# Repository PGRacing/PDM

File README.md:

# PDM

Schematic mockup:

TODO on next PCB:

Rev 4.3
| ID | NAME | CAUSE |DIFFICULTY | PRIORITY | STATUS |
| --- | --- | --- | --- | --- | --- |
| 1. | Create test board for BTS50025-1TAE | Switch with higher Rds(on) should perform better in terms of diagnostics on most used loads | 1 | 3 | | 
| 2. | Create schematic and brd for imporoved power delivery section optimized for autmotive use based on MP4322 TLS850F2TAV50, TVS diodes + filtering | Current solution with MP2332 has maximum rating of 18V, which is really for load dumps | 3 | 3 || 
| 3. | Divide task to "safety critical real-time" hardware based (timer) ones and other normal operation tasks | Current solution can cause safety issus | 3 | 3 || 
| 4. | Prepare I^2t wiring harness protection | This should allow better WH protection| 3 | 2 || 
| 5. | Prepare OCP using curve, not only single value | This should allow better WH protection | 2 | 3 || 
| 6. | Use buffers for MCU protection | Protect MCU I/O pins | 1 | 2 || 
| 7. | Change zenner protection diodes to extended linearity region of Is switch output || 1 | 3 || 
| 8. | Add better filtering (change RC filter values) on Is output | Is output on inductive signals or fast switched signals HFreq PWM used causes invalid readings | 1 | 3 || 
| 9. | Detect battery under-voltage and UV shutdown for battery protection || 1 | 2 || 
| 10. | Configuration over USB | For sake of user-friendly solution | 3 | 2 || 
| 11. | CAN inputs support || 2 | 2 || 
| 12. | Thermal sensing | Safety critical | 2 | 2 || 
| 13. | Better 3D printed caseing (take care of screws outside of caseing envelope) + add honeycomb reinforcment | Safety critical for splash proof | 2 | 1 || 
| 14. | Add logic-level shifter for LED's | Some LED's turn red on random order | 1 | 3 || 
| 15. | Add separate voltage source for ARGB LED's and CAN bus | working can bus is critical for system integrity | 1 | 3 || 
| 16. | Add external voltage sources diagnosis (at least voltage on output) || 2 | 3 || 
| 17. | Add battery insulation and reverse-polarity + huge TVS and maybe Gas Discharge Tubes | Load dumps + cold crank etc. | 3 | 2 || 
| 18. | Add better connector for BAT+ | 1 | 3 || 
| 19. | Add limp home mode when any peripheral is malfunctioning (detect those malfunctions) | 2 | 3 || 
| 20. | Add TVS or zenner on all inputs (in limit of absolute maximium rating) near connector | 1 | 3 || 
| 21. | Add external or on-board probes for temperature sensing | 2 | 2 || 
| 22. | Add more state/debug led's | 1 | 1 || 
| 23. | Move safety functions oc and counters and errors into separate struct or bit mask of register | 2 | 3 || 

Rev. 4.1
| NAME | DIFFICULTY | PRIORITY | STATUS |
| --- | --- | --- | --- |
| 1. Add fuse for external sensors supply (100mA). Can also be solved with second 5V regulator for sensors + fuse. | 1 | 3 | DONE - Added external LDO's to 3.3V and 5V |
| 2. Change CPC1117N to CPC1017N (or diffrent PhotoMos) | 1 | 2 | DONE - Added diffrent (smaller) Opto-MOS |
| 3. Add clamping diodes on any signals | 2 | 3 | Added zenner + shottky clippers |
| 4. Change input filtration for low profile SMD capacitor instead of tht | 1 | 1 | DEPRECEATED  |
| 5. Add SWO pin | 2 | 2 | DONE |
| 6. Current sensors output should be collected by one ADC !!! - for eg. ADC3 (change pinout) | 3 | 2 | DONE |
| 7. Add clamping diodes on current sensor to allow lower range current detecion | 2 | 3 | DONE |
| 8. Selection and redirection of IO is not imporant | 1 | 1 | DONE - (only four channels) |
| 9. Fix WS2812B footprint | 1 | 3 | DONE |
| 10. Use smaller footprint for voltage mux and can transceiver | 2 | 1 | DONE - changed voltage mux to 16 channel, CAN transceiver same |
| 11. Change FET's to BTS50010-1LUA | 3 | 2 |  DONE |
| 12. Add RX/TX information leds to CAN bus (software driven) | 1 | 1 | DEPERECATED |
| 13. Add MUX for mutlichannel switch | 2 | 2 | DONE - added 16 channel mux |
| 14. Add CAN software switching | 2 | 2 | DONE |
| 14. Remove additional header for stlink | 2 | 2 | DONE |

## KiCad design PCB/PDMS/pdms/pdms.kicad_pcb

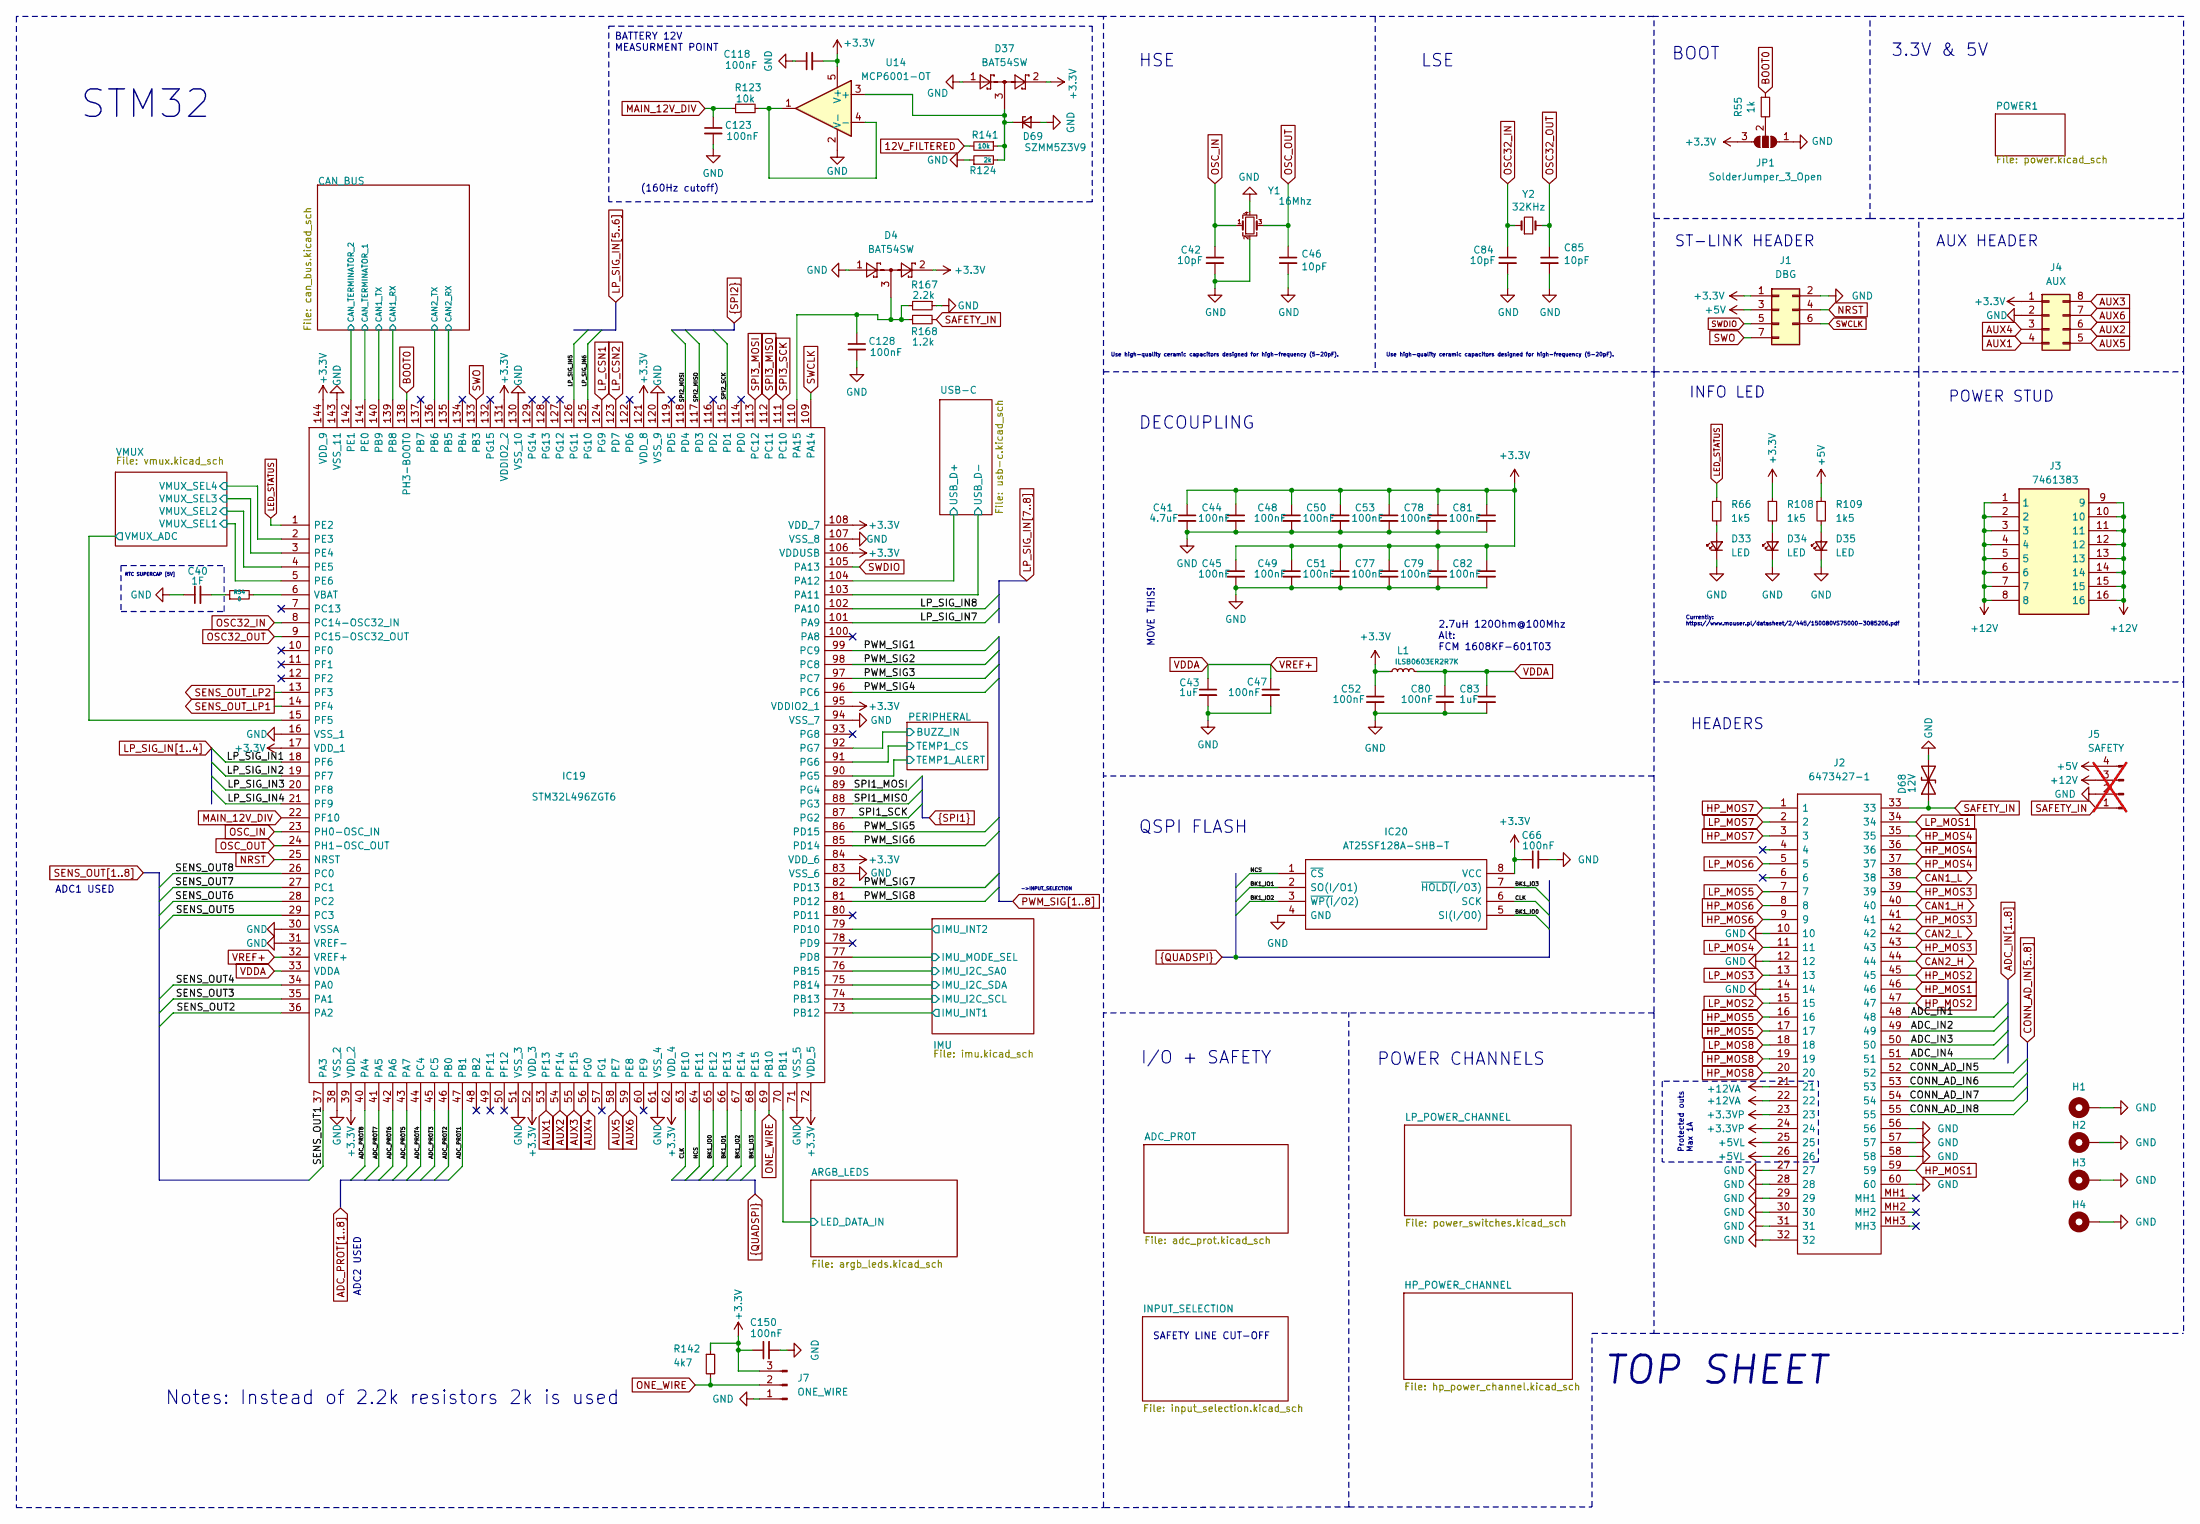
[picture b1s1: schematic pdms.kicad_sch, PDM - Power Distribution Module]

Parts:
C40: 1F; CAPCP3225X100N
C41: 4.7uF; R_0402_1005Metric
C42, C46: 10pF; R_0402_1005Metric
C43: 1uF; R_0402_1005Metric
C44, C45, C47, C48, C49, C50, C51, C52, C53, C66, C150: 100nF; R_0402_1005Metric
C77, C78, C79, C80, C81, C82, C118, C123, C128: 100nF; C_0402_1005Metric
C83: 1uF; C_0402_1005Metric
C84, C85: 10pF; C_0402_1005Metric
D4, D37: BAT54SW; SOT-323_SC-70
D33: LED; LED_0402_1005Metric
D34, D35: LED; LED_0805_2012Metric
D68: 12V; D_SOD-323
D69: SZMM5Z3V9; D_SOD-523
H1, H2, H3, H4: MountingHole_Pad; MountingHole_3.2mm_M3_Pad_Via
IC19: STM32L496ZGT6; QFP50P2200X2200X160-144N; Manufacturer_Part_Number STM32L496ZGT6; Mouser Part Number 511-STM32L496ZGT6
IC20: AT25SF128A-SHB-T; SOIC127P798X216-8N; Manufacturer_Part_Number AT25SF128A-SHB-T; Mouser Part Number 988-AT25SF128A-SHB-T
J1: DBG; Molex_PicoBlade_53047-0710_1x07_P1.25mm_Vertical
J2: 6473427-1; 64734271; Manufacturer_Part_Number 6473427-1; Mouser Part Number 571-6473427-1
J3: 7461383; Manufacturer_Part_Number 7461383; Mouser Part Number 710-7461383
J4: AUX; PinHeader_2x04_P1.00mm_Vertical_SMD
J5: SAFETY; Molex_PicoBlade_53047-0410_1x04_P1.25mm_Vertical; not fitted
J7: ONE_WIRE; PinHeader_1x03_P2.00mm_Vertical
JP1: SolderJumper_3_Open; SolderJumper-3_P1.3mm_Open_Pad1.0x1.5mm
L1: ILSB0603ER2R7K; L_0603_1608Metric
R54: 0; R_0805_2012Metric
R55: 1k; R_0402_1005Metric
R66, R108, R109: 1k5; R_0402_1005Metric
R123, R141: 10k; R_0402_1005Metric
R124: 2k; R_0402_1005Metric
R142: 4k7; R_0402_1005Metric
R167: 2.2k; R_0402_1005Metric
R168: 1.2k; R_0402_1005Metric
U14: MCP6001-OT; SOT-23-5
Y1: 16Mhz; Crystal_SMD_2016-4Pin_2.0x1.6mm
Y2: 32KHz; Crystal_SMD_3215-2Pin_3.2x1.5mm

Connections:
+3.3VP: J2.23, J2.24; also elsewhere on the board
+5V: J1.3, J5.4, R109.1; also elsewhere on the board
+5VL: J2.25, J2.26; also elsewhere on the board
+12V: J3.1, J3.2, J3.3, J3.4, J3.5, J3.6, J3.7, J3.8, J3.9, J3.10, J3.11, J3.12, J3.13, J3.14, J3.15, J3.16, J5.3; also elsewhere on the board
+12VA: J2.21, J2.22; also elsewhere on the board
/ARGB_LEDS/LED_DATA_IN: IC19.70 (PB11); also elsewhere on the board
/CAN_BUS/CAN1_RX: IC19.139 (PB8); also elsewhere on the board
/CAN_BUS/CAN1_TX: IC19.140 (PB9); also elsewhere on the board
/CAN_BUS/CAN2_RX: IC19.135 (PB5); also elsewhere on the board
/CAN_BUS/CAN2_TX: IC19.136 (PB6); also elsewhere on the board
/CAN_BUS/CAN_TERMINATOR_1: IC19.141 (PE0); also elsewhere on the board
/CAN_BUS/CAN_TERMINATOR_2: IC19.142 (PE1); also elsewhere on the board
/IMU/IMU_I2C_SA0: IC19.76 (PB15); also elsewhere on the board
/IMU/IMU_I2C_SCL: IC19.74 (PB13); also elsewhere on the board
/IMU/IMU_I2C_SDA: IC19.75 (PB14); also elsewhere on the board
/IMU/IMU_INT1: IC19.73 (PB12); also elsewhere on the board
/IMU/IMU_INT2: IC19.79 (PD10); also elsewhere on the board
/IMU/IMU_MODE_SEL: IC19.77 (PD8); also elsewhere on the board
/PERIPHERAL/BUZZ_IN: IC19.92 (PG7); also elsewhere on the board
/PERIPHERAL/TEMP1_ALERT: IC19.90 (PG5); also elsewhere on the board
/PERIPHERAL/TEMP1_CS: IC19.91 (PG6); also elsewhere on the board
/USB-C/USB_D+: IC19.104 (PA12); also elsewhere on the board
/USB-C/USB_D-: IC19.103 (PA11); also elsewhere on the board
/VMUX/VMUX_SEL1: IC19.5 (PE6); also elsewhere on the board
/VMUX/VMUX_SEL2: IC19.4 (PE5); also elsewhere on the board
/VMUX/VMUX_SEL3: IC19.3 (PE4); also elsewhere on the board
/VMUX/VMUX_SEL4: IC19.2 (PE3); also elsewhere on the board
ADC_IN1: J2.48; also elsewhere on the board
ADC_IN2: J2.49; also elsewhere on the board
ADC_IN3: J2.50; also elsewhere on the board
ADC_IN4: J2.51; also elsewhere on the board
ADC_PROT1: IC19.47 (PB1); also elsewhere on the board
ADC_PROT2: IC19.46 (PB0); also elsewhere on the board
ADC_PROT3: IC19.45 (PC5); also elsewhere on the board
ADC_PROT4: IC19.44 (PC4); also elsewhere on the board
ADC_PROT5: IC19.43 (PA7); also elsewhere on the board
ADC_PROT6: IC19.42 (PA6); also elsewhere on the board
ADC_PROT7: IC19.41 (PA5); also elsewhere on the board
ADC_PROT8: IC19.40 (PA4); also elsewhere on the board
AUX1: IC19.53 (PF13), J4.4
AUX2: IC19.54 (PF14), J4.6
AUX3: IC19.55 (PF15), J4.8
AUX4: IC19.56 (PG0), J4.3
AUX5: IC19.58 (PE7), J4.5
AUX6: IC19.59 (PE8), J4.7
BK1_IO0: IC19.65 (PE12), IC20.5 (SI(I/O0))
BK1_IO1: IC19.66 (PE13), IC20.2 (SO(I/O1))
BK1_IO2: IC19.67 (PE14), IC20.3 (~WP(I/O2))
BK1_IO3: IC19.68 (PE15), IC20.7 (~HOLD(I/O3))
BOOT0: IC19.138 (PH3-BOOT0), R55.1
CAN1_H: J2.40; also elsewhere on the board
CAN1_L: J2.38; also elsewhere on the board
CAN2_H: J2.44; also elsewhere on the board
CAN2_L: J2.42; also elsewhere on the board
CLK: IC19.63 (PE10), IC20.6 (SCK)
CONN_AD_IN5: J2.52; also elsewhere on the board
CONN_AD_IN6: J2.53; also elsewhere on the board
CONN_AD_IN7: J2.54; also elsewhere on the board
CONN_AD_IN8: J2.55; also elsewhere on the board
HP_MOS1: J2.46, J2.59; also elsewhere on the board
HP_MOS2: J2.45, J2.47; also elsewhere on the board
HP_MOS3: J2.39, J2.41, J2.43; also elsewhere on the board
HP_MOS4: J2.35, J2.36, J2.37; also elsewhere on the board
HP_MOS5: J2.16, J2.17; also elsewhere on the board
HP_MOS6: J2.8, J2.9; also elsewhere on the board
HP_MOS7: J2.1, J2.3; also elsewhere on the board
HP_MOS8: J2.19, J2.20; also elsewhere on the board
LED_STATUS: IC19.1 (PE2), R66.1
LP_CSN1: IC19.124 (PG9); also elsewhere on the board
LP_CSN2: IC19.123 (PD7); also elsewhere on the board
LP_MOS1: J2.34; also elsewhere on the board
LP_MOS2: J2.15; also elsewhere on the board
LP_MOS3: J2.13; also elsewhere on the board
LP_MOS4: J2.11; also elsewhere on the board
LP_MOS5: J2.7; also elsewhere on the board
LP_MOS6: J2.5; also elsewhere on the board
LP_MOS7: J2.2; also elsewhere on the board
LP_MOS8: J2.18; also elsewhere on the board
LP_SIG_IN1: IC19.18 (PF6); also elsewhere on the board
LP_SIG_IN2: IC19.19 (PF7); also elsewhere on the board
LP_SIG_IN3: IC19.20 (PF8); also elsewhere on the board
LP_SIG_IN4: IC19.21 (PF9); also elsewhere on the board
LP_SIG_IN5: IC19.126 (PG11); also elsewhere on the board
LP_SIG_IN6: IC19.125 (PG10); also elsewhere on the board
LP_SIG_IN7: IC19.101 (PA9); also elsewhere on the board
LP_SIG_IN8: IC19.102 (PA10); also elsewhere on the board
NCS: IC19.64 (PE11), IC20.1 (~CS)
NRST: IC19.25 (NRST), J1.4
unnamed: C40.2, R54.1
unnamed: D33.2 (A), R66.2
unnamed: D34.2 (A), R108.2
unnamed: D35.2 (A), R109.2
unnamed: C128.1, D4.3, IC19.110 (PA15), R167.2, R168.1
unnamed: IC19.6 (VBAT), R54.2
unnamed: JP1.2 (C), R55.2
ONE_WIRE: IC19.69 (PB10), J7.2, R142.2
OSC32_IN: C84.1, IC19.8 (PC14-OSC32_IN), Y2.1
OSC32_OUT: C85.1, IC19.9 (PC15-OSC32_OUT), Y2.2
OSC_IN: C42.1, IC19.23 (PH0-OSC_IN), Y1.1
OSC_OUT: C46.1, IC19.24 (PH1-OSC_OUT), Y1.3
PWM_SIG1: IC19.99 (PC9); also elsewhere on the board
PWM_SIG2: IC19.98 (PC8); also elsewhere on the board
PWM_SIG3: IC19.97 (PC7); also elsewhere on the board
PWM_SIG4: IC19.96 (PC6); also elsewhere on the board
PWM_SIG5: IC19.86 (PD15); also elsewhere on the board
PWM_SIG6: IC19.85 (PD14); also elsewhere on the board
PWM_SIG7: IC19.82 (PD13); also elsewhere on the board
PWM_SIG8: IC19.81 (PD12); also elsewhere on the board
SAFETY_IN: D68.1 (A1), J2.33, J5.1, R168.2; also elsewhere on the board
SENS_OUT1: IC19.37 (PA3); also elsewhere on the board
SENS_OUT2: IC19.36 (PA2); also elsewhere on the board
SENS_OUT3: IC19.35 (PA1); also elsewhere on the board
SENS_OUT4: IC19.34 (PA0); also elsewhere on the board
SENS_OUT5: IC19.29 (PC3); also elsewhere on the board
SENS_OUT6: IC19.28 (PC2); also elsewhere on the board
SENS_OUT7: IC19.27 (PC1); also elsewhere on the board
SENS_OUT8: IC19.26 (PC0); also elsewhere on the board
SENS_OUT_LP1: IC19.14 (PF4); also elsewhere on the board
SENS_OUT_LP2: IC19.13 (PF3); also elsewhere on the board
SPI1_MISO: IC19.88 (PG3); also elsewhere on the board
SPI1_MOSI: IC19.89 (PG4); also elsewhere on the board
SPI1_SCK: IC19.87 (PG2); also elsewhere on the board
SPI2_MISO: IC19.117 (PD3); also elsewhere on the board
SPI2_MOSI: IC19.118 (PD4); also elsewhere on the board
SPI2_SCK: IC19.115 (PD1); also elsewhere on the board
SPI3_MISO: IC19.112 (PC11)
SPI3_MOSI: IC19.113 (PC12)
SPI3_SCK: IC19.111 (PC10)
SWCLK: IC19.109 (PA14), J1.6; also elsewhere on the board
SWDIO: IC19.105 (PA13), J1.5; also elsewhere on the board
SWO: IC19.133 (PB3), J1.7

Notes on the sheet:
BATTERY 12V MEASURMENT POINT
POWER STUD
BOOT
AUX HEADER
HSE
MOVE THIS!
Notes: Instead of 2.2k resistors 2k is used
INFO LED
STM32
DECOUPLING
POWER CHANNELS
(160Hz cutoff)
->INPUT_SELECTION
2.7uH 120Ohm@100Mhz Alt: FCM 1608KF-601T03
Use high-quality ceramic capacitors designed for high-frequency (5-20pF).
QSPI FLASH
Protected outs Max 1A
TOP SHEET
RTC SUPERCAP [5V]
HEADERS
ST-LINK HEADER
LSE
I/O + SAFETY
SAFETY LINE CUT-OFF
Currently: https://www.mouser.pl/datasheet/2/445/150080VS75000-3085206.pdf
ADC2 USED
ADC1 USED
3.3V & 5V

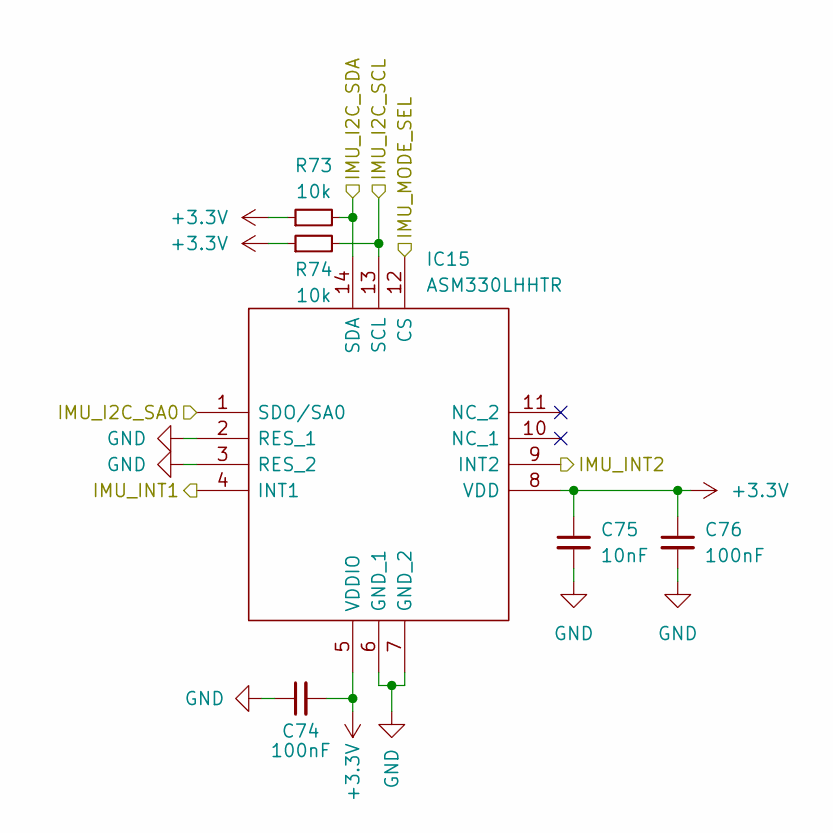
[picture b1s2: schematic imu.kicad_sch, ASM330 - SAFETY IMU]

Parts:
C74, C76: 100nF; C_0402_1005Metric
C75: 10nF; C_0402_1005Metric
IC15: ASM330LHHTR; LGA-14_2.5X3X0.86_; Manufacturer_Part_Number ASM330LHHTR; Mouser Part Number 511-ASM330LHHTR
R73, R74: 10k; R_0402_1005Metric

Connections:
/IMU/IMU_I2C_SA0: IC15.1 (SDO/SA0); also elsewhere on the board
/IMU/IMU_I2C_SCL: IC15.13 (SCL), R74.2; also elsewhere on the board
/IMU/IMU_I2C_SDA: IC15.14 (SDA), R73.2; also elsewhere on the board
/IMU/IMU_INT1: IC15.4 (INT1); also elsewhere on the board
/IMU/IMU_INT2: IC15.9 (INT2); also elsewhere on the board
/IMU/IMU_MODE_SEL: IC15.12 (CS); also elsewhere on the board

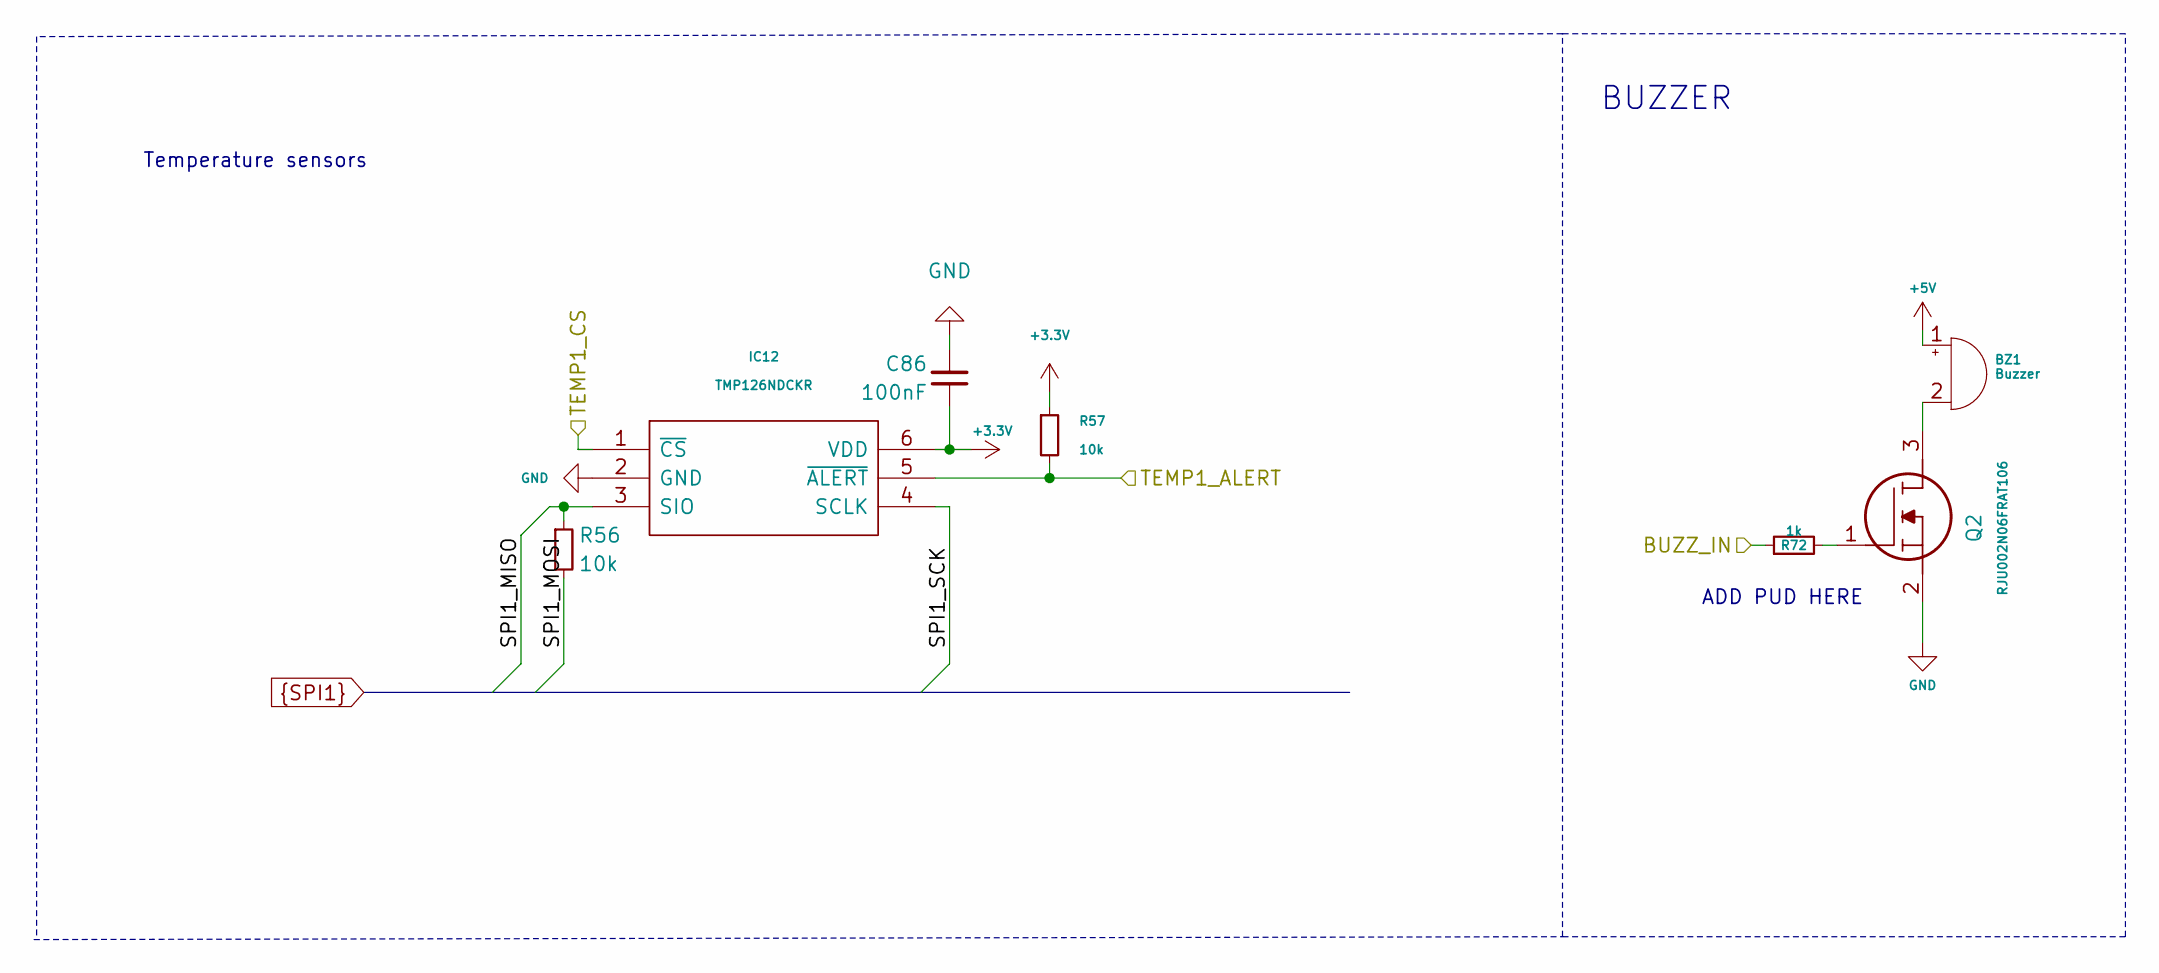
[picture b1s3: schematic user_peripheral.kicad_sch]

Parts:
BZ1: Buzzer; Buzzer_12x9.5RM7.6
C86: 100nF; C_0402_1005Metric
IC12: TMP126NDCKR; SOT65P210X110-6N; Manufacturer_Part_Number TMP126NDCKR; Mouser Part Number 595-TMP126NDCKR
Q2: RJU002N06FRAT106; SOT65P210X110-3N; Manufacturer_Part_Number RJU002N06FRAT106; Mouser Part Number 755-RJU002N06FRAT106
R56, R57: 10k; R_0402_1005Metric
R72: 1k; R_0402_1005Metric

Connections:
+5V: BZ1.1 (-); also elsewhere on the board
/PERIPHERAL/BUZZ_IN: R72.1; also elsewhere on the board
/PERIPHERAL/TEMP1_ALERT: IC12.5 (~ALERT), R57.2; also elsewhere on the board
/PERIPHERAL/TEMP1_CS: IC12.1 (~CS); also elsewhere on the board
unnamed: BZ1.2 (+), Q2.3
unnamed: Q2.1, R72.2
SPI1_MISO: IC12.3 (SIO), R56.1; also elsewhere on the board
SPI1_MOSI: R56.2; also elsewhere on the board
SPI1_SCK: IC12.4 (SCLK); also elsewhere on the board

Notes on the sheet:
BUZZER
ADD PUD HERE
Temperature sensors

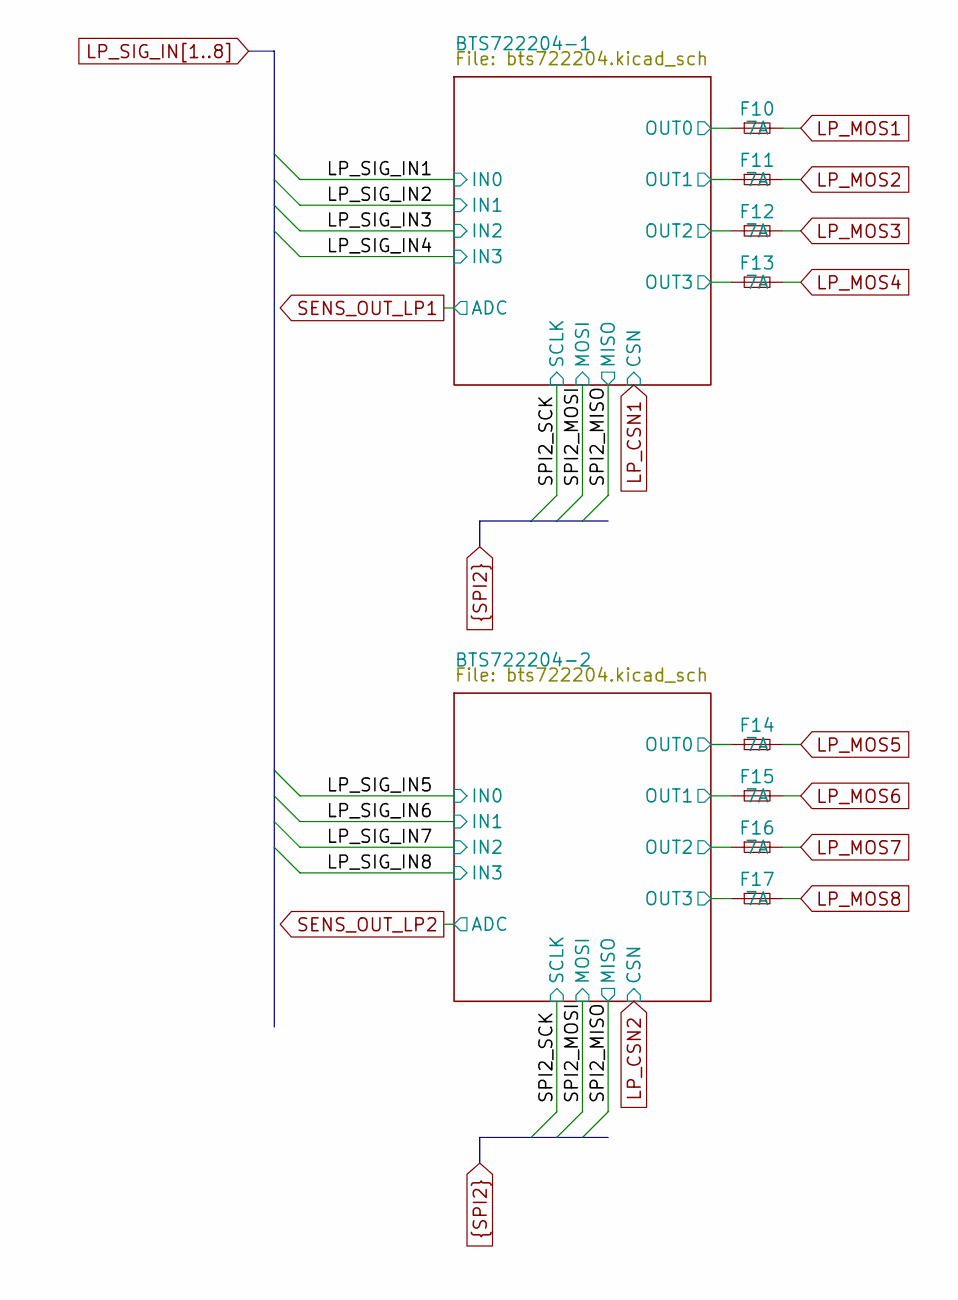
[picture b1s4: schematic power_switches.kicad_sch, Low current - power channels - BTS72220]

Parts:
F10, F11, F12, F13, F14, F15, F16, F17: 7A; Fuse_1206_3216Metric

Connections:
/LP_POWER_CHANNEL/BTS722204-1/OUT0: F10.1; also elsewhere on the board
/LP_POWER_CHANNEL/BTS722204-1/OUT1: F11.1; also elsewhere on the board
/LP_POWER_CHANNEL/BTS722204-1/OUT2: F12.1; also elsewhere on the board
/LP_POWER_CHANNEL/BTS722204-1/OUT3: F13.1; also elsewhere on the board
/LP_POWER_CHANNEL/BTS722204-2/OUT0: F14.1; also elsewhere on the board
/LP_POWER_CHANNEL/BTS722204-2/OUT1: F15.1; also elsewhere on the board
/LP_POWER_CHANNEL/BTS722204-2/OUT2: F16.1; also elsewhere on the board
/LP_POWER_CHANNEL/BTS722204-2/OUT3: F17.1; also elsewhere on the board
LP_MOS1: F10.2; also elsewhere on the board
LP_MOS2: F11.2; also elsewhere on the board
LP_MOS3: F12.2; also elsewhere on the board
LP_MOS4: F13.2; also elsewhere on the board
LP_MOS5: F14.2; also elsewhere on the board
LP_MOS6: F15.2; also elsewhere on the board
LP_MOS7: F16.2; also elsewhere on the board
LP_MOS8: F17.2; also elsewhere on the board

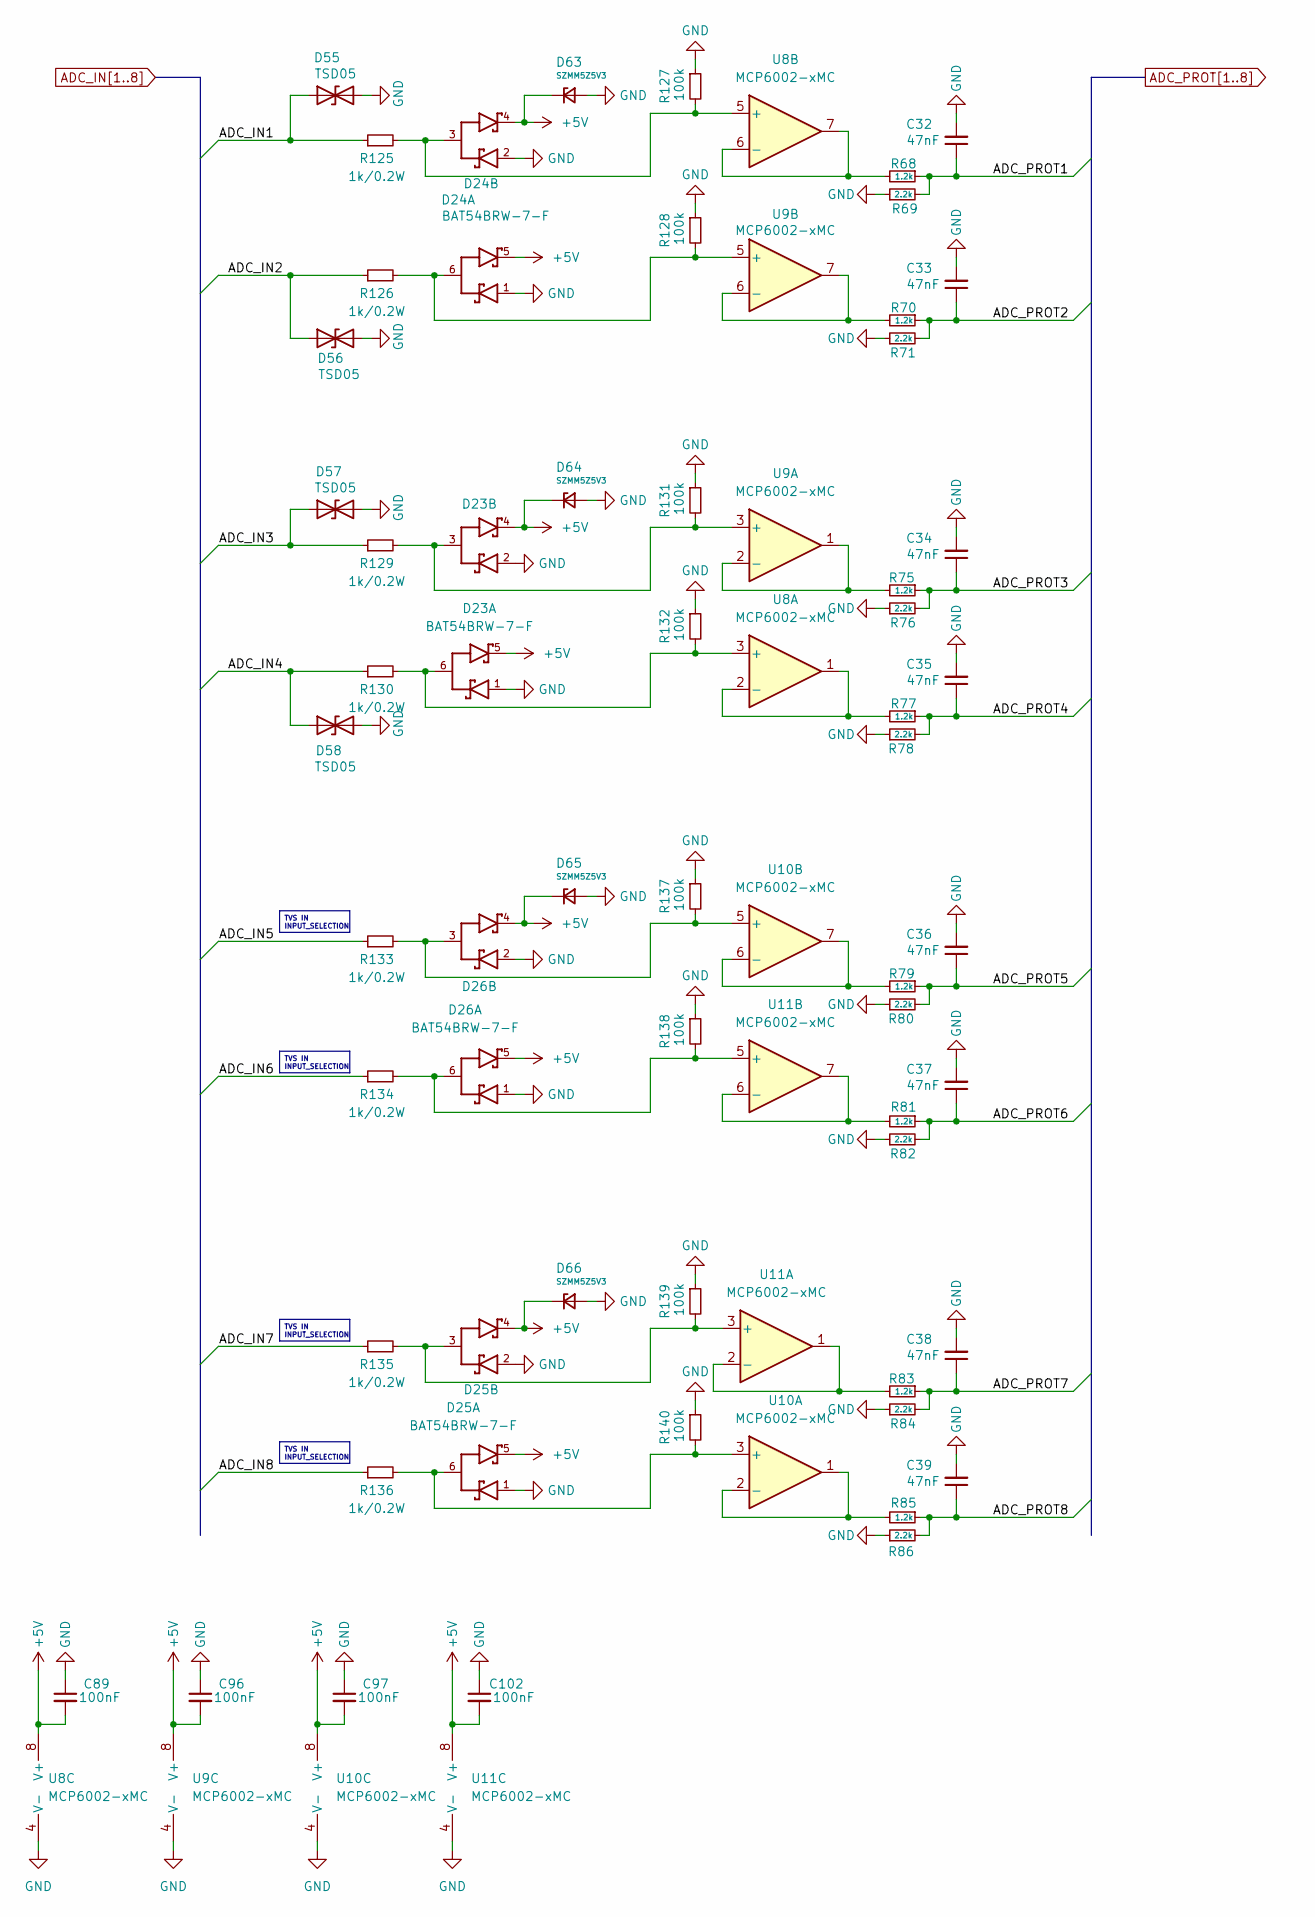
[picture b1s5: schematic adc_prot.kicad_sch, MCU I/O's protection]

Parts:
C32, C33, C34, C35, C36, C37, C38, C39: 47nF; C_0402_1005Metric
C89, C96, C97, C102: 100nF; R_0402_1005Metric
D23, D24, D25, D26: BAT54BRW-7-F; SOT65P210X110-6N; PARTREV 17 - 2
D55, D56, D57, D58: TSD05; D_SOD-323
D63, D64, D65, D66: SZMM5Z5V3; D_SOD-523
R68, R70, R75, R77, R79, R81, R83, R85: 1.2k; R_0402_1005Metric
R69, R71, R76, R78, R80, R82, R84, R86: 2.2k; R_0402_1005Metric
R125, R126, R129, R130, R133, R134, R135, R136: 1k/0.2W; R_0603_1608Metric
R127, R128, R131, R132, R137, R138, R139, R140: 100k; R_0402_1005Metric
U8, U9, U10, U11: MCP6002-xMC; DFN-8-1EP_3x2mm_P0.5mm_EP1.75x1.45mm

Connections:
+5V: C89.2, C96.2, C97.2, C102.2, D23.4, D23.5, D24.4, D24.5, D25.4, D25.5, D26.4, D26.5, D63.1 (K), D64.1 (K), D65.1 (K), D66.1 (K), U8.8 (V+), U9.8 (V+), U10.8 (V+), U11.8 (V+); also elsewhere on the board
ADC_IN1: D55.1 (A1), R125.1; also elsewhere on the board
ADC_IN2: D56.1 (A1), R126.1; also elsewhere on the board
ADC_IN3: D57.1 (A1), R129.1; also elsewhere on the board
ADC_IN4: D58.1 (A1), R130.1; also elsewhere on the board
ADC_IN5: R133.1; also elsewhere on the board
ADC_IN6: R134.1; also elsewhere on the board
ADC_IN7: R135.1; also elsewhere on the board
ADC_IN8: R136.1; also elsewhere on the board
ADC_PROT1: C32.1, R68.1, R69.2; also elsewhere on the board
ADC_PROT2: C33.1, R70.1, R71.2; also elsewhere on the board
ADC_PROT3: C34.1, R75.1, R76.2; also elsewhere on the board
ADC_PROT4: C35.1, R77.1, R78.2; also elsewhere on the board
ADC_PROT5: C36.1, R79.1, R80.2; also elsewhere on the board
ADC_PROT6: C37.1, R81.1, R82.2; also elsewhere on the board
ADC_PROT7: C38.1, R83.1, R84.2; also elsewhere on the board
ADC_PROT8: C39.1, R85.1, R86.2; also elsewhere on the board
unnamed: D23.6, R130.2, R132.2, U8.3 (+)
unnamed: R77.2, U8.1, U8.2 (-)
unnamed: D24.3, R125.2, R127.2, U8.5 (+)
unnamed: R68.2, U8.6 (-), U8.7
unnamed: D23.3, R129.2, R131.2, U9.3 (+)
unnamed: R75.2, U9.1, U9.2 (-)
unnamed: D24.6, R126.2, R128.2, U9.5 (+)
unnamed: R70.2, U9.6 (-), U9.7
unnamed: D25.6, R136.2, R140.2, U10.3 (+)
unnamed: R85.2, U10.1, U10.2 (-)
unnamed: D26.3, R133.2, R137.2, U10.5 (+)
unnamed: R79.2, U10.6 (-), U10.7
unnamed: D25.3, R135.2, R139.2, U11.3 (+)
unnamed: R83.2, U11.1, U11.2 (-)
unnamed: D26.6, R134.2, R138.2, U11.5 (+)
unnamed: R81.2, U11.6 (-), U11.7

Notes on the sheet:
TVS IN INPUT_SELECTION

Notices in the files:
parts and their libraries:
Copyright 2021 Accelerated Designs. All rights reserved.
